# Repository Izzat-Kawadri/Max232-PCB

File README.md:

# Max232 PCB Design and Implementation

- **Project Name:** Max232 PCB Design and Implementation 
- **Project for:** Introduction to PCB Course 
- **Project Date:** 2018

## Table of Contents
1. [Introduction](#introduction)
2. [What is MAX232?](#what-is-max232)
3. [Main Components and BOM](#main-components-and-bom)
4. [Schematic of the Circuit](#schematic-of-the-circuit)
5. [PCB Design](#pcb-design)
6. [Implementation Process](#implementation-process)
7. [Getting Started](#getting-started)

## Introduction

This repository contains the design files, schematic, and implementation details for a printed circuit board (PCB) that utilizes the MAX232 IC. The project is created using the Eagle PCB design software. The MAX232 is commonly used for RS-232 serial communication, and this project demonstrates how to design and implement a PCB for it.

This project was completed as part of a **training project** in the **PCB Design course** that we attended at our university. It aims to teach the fundamentals of PCB design, schematic creation, component placement, routing, and testing through hands-on experience with a real-world application.

## What is MAX232?
The MAX232 is an integrated circuit (IC) used to convert signals from a TIA-232 (RS-232) serial port to signals suitable for use in TTL-compatible digital logic circuits. It is a dual driver/receiver and typically requires a single 5V power supply. The IC includes capacitive voltage generators to supply the necessary voltage levels for RS-232 communication, making it a popular choice in embedded systems that need serial communication.

### Key Features:
- Dual transmitter/receiver pairs
- Operates from a single 5V power supply
- Converts RS-232 signals to TTL levels
- Requires external capacitors for voltage generation

## Main Components and BOM
Below is the Bill of Materials (BOM) for the MAX232 PCB design:

| **Component**        | **Description**                          | **Quantity** | **Part Number**  |
|----------------------|------------------------------------------|--------------|------------------|
| MAX232 IC            | RS-232 to TTL Logic Level Converter      | 1            | MAX232N          |
| 0.1µF Capacitors     | Ceramic Capacitors for Voltage Conversion | 5            | C1, C2, C3, C4, C5 |
| 16-Pin IC Socket     | Socket for MAX232 IC                     | 1            | IC1              |
| DB9 Connector        | Female RS-232 Connector                  | 1            | CON1             |
| 10µF Electrolytic Capacitors | For Voltage Regulation            | 2            | C6, C7           |
| Resistors            | Various Resistors for Circuit Stability  | 3            | R1, R2, R3       |
| LEDs                 | Power and Signal Indicators              | 2            | LED1, LED2       |
| PCB                  | Printed Circuit Board                    | 1            | -                |

## Schematic of the Circuit
The schematic of the circuit shows how each component is connected to the MAX232 IC. The schematic is designed in Eagle and is available in the `schematics` directory of this repository. The key connections include:

- **RS-232 Interface**: Connects to the DB9 connector.
- **TTL Interface**: Connects to the TTL logic circuit.
- **Power Supply**: 5V input to power the MAX232 and related components.
  
- **[Schematic README](schematics/README.md)**: Detailed information on the circuit schematic and the files in the `schematics` folder.

## PCB Design
The PCB design is a crucial part of the project, ensuring that all components are properly laid out to fit within the desired form factor. The design files are available in the `pcb_design` directory. The PCB layout includes:

- **Component Placement**: Proper placement of the MAX232 IC, capacitors, resistors, and connectors.
- **Routing**: Signal routing ensuring minimal interference and optimized performance.
- **Layers**: Single-layer design for simplicity, with ground and power planes.

- **[PCB Design README](pcb_design/README.md)**: Details about the PCB layout and how to work with the design files.

## Implementation Process
The implementation process involves the following steps:

1. **Schematic Design**: Design the circuit schematic in Eagle.
2. **Component Selection**: Select components based on the requirements of the MAX232 IC.
3. **PCB Layout**: Design the PCB layout, ensuring optimal component placement and routing.
4. **Fabrication**: Send the PCB design to a manufacturer for fabrication.
5. **Assembly**: Solder the components onto the fabricated PCB.
6. **Testing**: Test the assembled PCB to ensure that the MAX232 IC is functioning correctly and that RS-232 communication is stable.

- **[Implementation README](implementation/README.md)**: Step-by-step guide on how to assemble and test the PCB.

## Related README Files
In addition to this main README, the following folders contain their own `README.md` files, which provide more detailed explanations for each section of the project:
- **[Schematic Folder](schematics/README.md)**: Information about the schematic files.
- **[PCB Design Folder](pcb_design/README.md)**: Details about the PCB layout and fabrication files.
- **[Implementation Folder](implementation/README.md)**: Assembly and testing instructions for the fabricated PCB.

## Credits and Special Thanks
This project was a team effort, and we would like to acknowledge everyone involved.

### Project Team
- **[Izzat Kawadri](https://www.linkedin.com/in/izzat-kawadri)** – Circuit Design ,Schematic, Documentation and BOM. 
- **[Mohammed al Dawaish](#)** – Implementation and Testing
- **[Yazan Almesh](https://www.linkedin.com/in/yazan-almesh-31a516250/)** – PCB Layout and Routing
  
### Special Thanks
We extend our special thanks to:

- **[Mohamad Msalme](#) ,[Mohammad Hassan](#)** – For providing expert guidance and mentorship throughout the course.
- **The Volunteering Team : Tomouh**(#) – For organizing and supporting the introduction to PCB design course.

## Getting Started
To get started with this project:

1. Clone the repository: `git clone https://github.com/Izzat-Kawadri/Max232-PCB.git`
2. Open the Eagle project files located in the `schematics` and `pcb_design` directories.
3. Follow the implementation steps to build your own MAX232 PCB.

## License
This project is licensed under the MIT License - see the [LICENSE](LICENSE) file for details.

---

This README provides an overview of Max232 PCB design and implementation. For detailed instructions and files, please explore the corresponding folders and their respective `README.md` files.

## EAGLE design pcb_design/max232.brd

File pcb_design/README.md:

# PCB Design Folder

## Overview
This folder contains the PCB design files for the MAX232 PCB project. The design translates the schematic into a physical board layout, ensuring that all components are placed correctly and connected via copper traces. The PCB is designed using Eagle PCB design software.

## Files in This Folder
- **max232_pcb.brd**: The Eagle PCB board file, containing the full PCB layout for the MAX232 circuit.
- **max232_pcb.png**: A high-resolution image of the PCB design for quick reference.

  > **Note:** The `.brd` file can be opened with Eagle PCB design software or any compatible tool that supports Eagle file formats.

## PCB Layout Overview
The PCB design includes:
- **Component Placement**: All components, such as the MAX232 IC, capacitors, resistors, DB9 connector, and LEDs, are placed optimally for easy assembly and signal integrity.
- **Routing**: Copper traces connect the components according to the schematic. The design is optimized for signal clarity and minimal interference.
- **Power and Ground Planes**: The PCB includes ground and power planes for better noise management and stability.
- **Single-Layer Design**: This PCB is designed as a single-layer board, making it simple to manufacture and cost-effective.

## PCB Design Process
The design was created by following these steps:
1. **Schematic to PCB Conversion**: The schematic from the [schematic folder](../schematics) was converted to a PCB design using Eagle’s board editor.
2. **Component Placement**: Components were arranged to ensure logical signal flow and compact layout.
3. **Routing**: Signal traces were routed between components while minimizing trace length and avoiding cross-talk.
4. **Design Rule Check (DRC)**: A DRC was performed to ensure that all traces and clearances meet manufacturing standards.

## Related Files
- The corresponding schematic can be found in the [schematic folder](../schematics).
- The Bill of Materials (BOM) and additional component information are available in the main project’s README file.

---

This folder contains all the necessary files to review, edit, and fabricate the PCB for the MAX232 project. Make sure to verify the PCB design before ordering or making modifications.

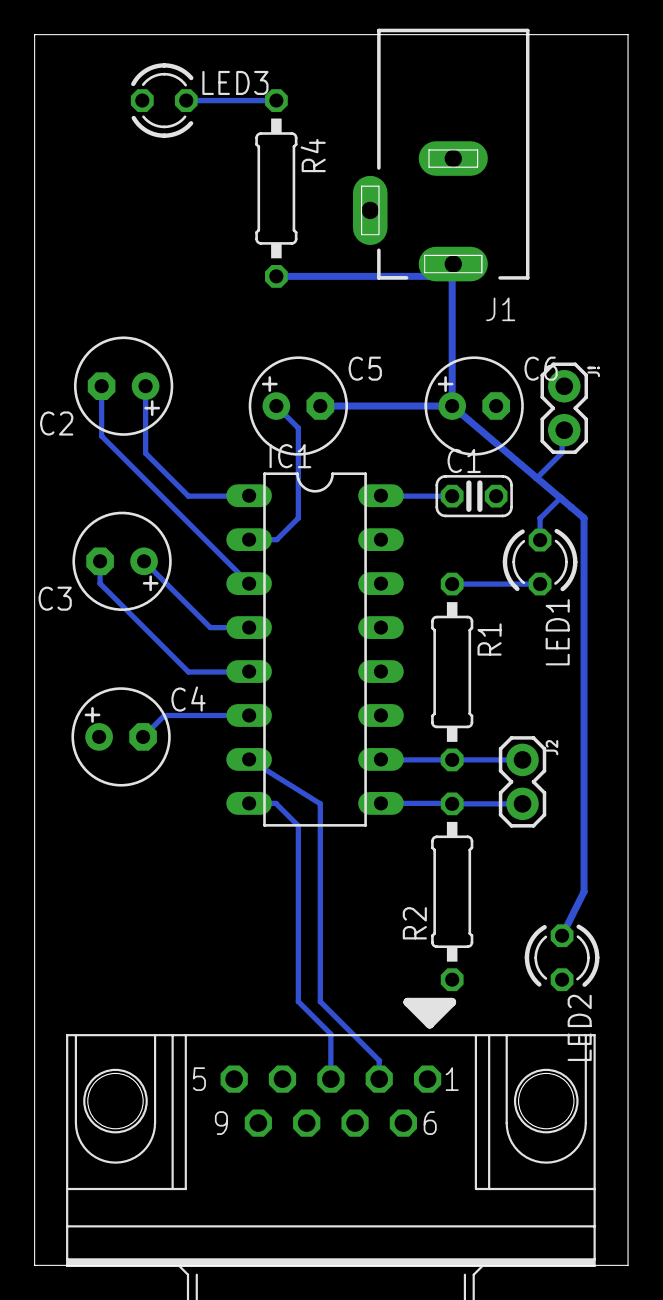
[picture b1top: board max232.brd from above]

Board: 2 copper layers, 34.3 x 71.1 mm, 17 parts (0 on the bottom side), 15 nets.

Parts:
C1: 100nf; C025-024X044
C2: 1uf / 25v; E2,5-6
C3, C4, C5: 1uf /25v; E2,5-6
C6: 4.7uf; E2,5-6
CON1: FEMALE; D-09F/90
IC1: MAX232; DIL16
J1: DCJ0202
J2: FEMALE; 1X02
J!: female; 1X02
LED1, LED3: red; LED3MM
LED2: green; LED3MM
R1: 220 /0.25w; 0207/10
R2: 220 / 0.25 w; 0207/10
R4: 220; 0207/10

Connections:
FAMEL: CON1.3, IC1.8
GND: C1.2, C4.+, C6.-, CON1.5, IC1.15, J1.2, J1.3, J!.1, LED3.A
unnamed: C2.+, IC1.1
unnamed: C2.-, IC1.3
unnamed: C3.+, IC1.4
unnamed: C3.-, IC1.5
unnamed: C5.+, IC1.2
unnamed: C4.-, IC1.6
unnamed: CON1.2, IC1.7
unnamed: LED1.K, R1.1
unnamed: LED2.K, R2.1
unnamed: LED3.K, R4.1
RX: IC1.9, J2.2, R2.2
TX: IC1.10, J2.1, R1.2
VCC: C1.1, C5.-, C6.+, IC1.16, J1.1, J!.2, LED1.A, LED2.A, R4.2

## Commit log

2024-09-20 Create LICENSE
